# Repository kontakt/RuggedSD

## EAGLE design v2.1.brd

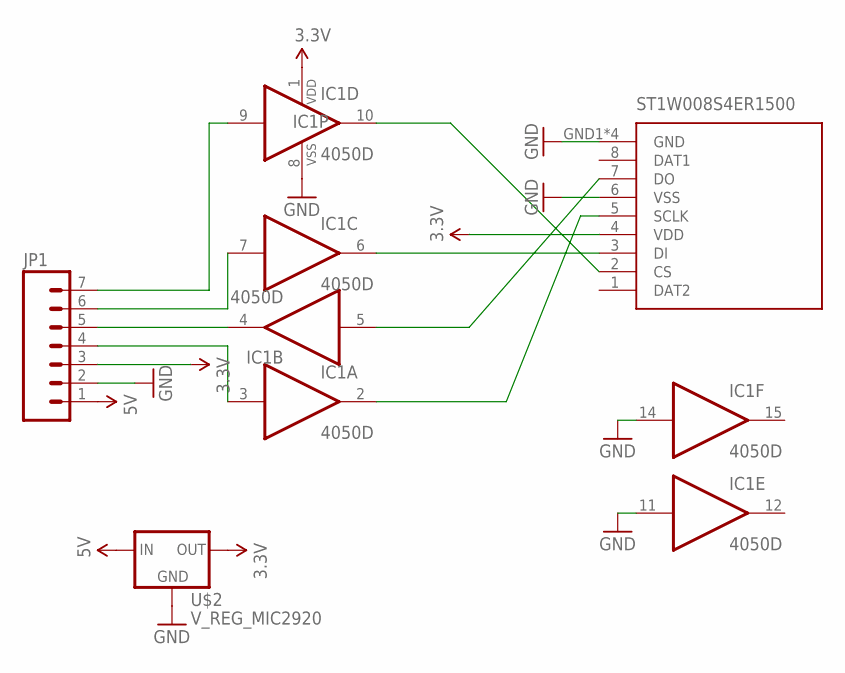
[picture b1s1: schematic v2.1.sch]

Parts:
IC1: 4050D; SO16
JP1: M07; 1X07
U$1: ST1W008S4ER1500
U$2: V_REG_MIC2920; SOT223

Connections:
3.3V: IC1.1 (VDD), JP1.3, U$1.4 (VDD), U$2.3 (OUT)
5V: JP1.1, U$2.1 (IN)
GND: IC1.8 (VSS), IC1.11 (I), IC1.14 (I), JP1.2, U$1.6 (VSS), U$1.GND1 (GND), U$1.GND2 (GND), U$1.GND3 (GND), U$1.GND4 (GND), U$2.2 (GND)
unnamed: IC1.9 (I), JP1.7
unnamed: IC1.7 (I), JP1.6
unnamed: IC1.5 (I), U$1.7 (DO)
unnamed: IC1.3 (I), JP1.4
unnamed: IC1.10 (O), U$1.2 (CS)
unnamed: IC1.6 (O), U$1.3 (DI)
unnamed: IC1.4 (O), JP1.5
unnamed: IC1.2 (O), U$1.5 (SCLK)

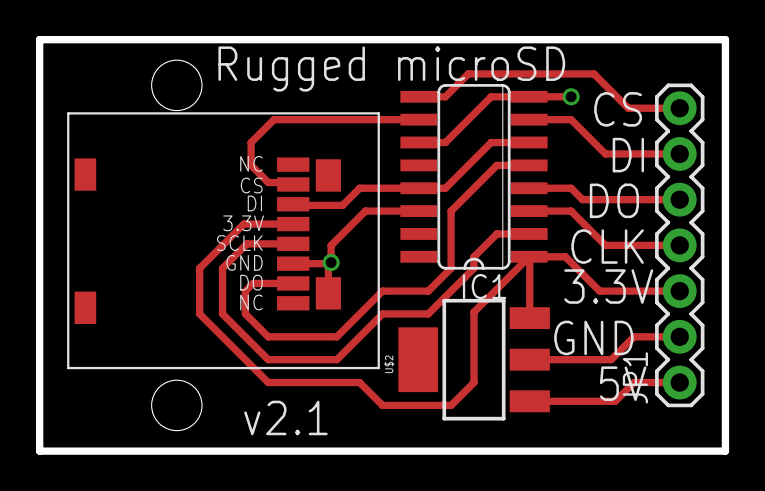
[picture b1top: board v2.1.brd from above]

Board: 2 copper layers, 38.1 x 22.9 mm, 4 parts (0 on the bottom side), 11 nets.

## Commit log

2015-09-09 :tada: Added .gitattributes & .gitignore files
2016-01-17 Revised
    Upgraded version

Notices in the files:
parts and their libraries:
SparkFun-Connectors: Licensing: Creative Commons ShareAlike 4.0 International - https://creativecommons.org/licenses/by-sa/4.0
